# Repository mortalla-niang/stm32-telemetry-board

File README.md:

# STM32 Telemetry Board

> An end-to-end embedded systems project covering hardware design, firmware development, and desktop software for an STM32-based telemetry board.

---

# Overview

This project documents the complete development of an embedded telemetry board built around an STM32 microcontroller.

The objective is to design every part of the system from scratch while following industry-standard embedded development practices.

The project includes:

- Custom PCB design using KiCad
- STM32 firmware development in C
- Temperature acquisition through an I²C sensor
- UART communication with a desktop application
- Python desktop interface
- Complete engineering documentation
- Version control using Git

---

# System Architecture

```
                  USB-C
                    │
                    ▼
             +--------------+
             | 3.3V Regulator|
             +------+-------+
                    │
                    ▼
           +------------------+
           |  STM32C091KB MCU |
           +--------+---------+
                    │
         ┌──────────┴──────────┐
         │                     │
         ▼                     ▼
    TMP102 Sensor         UART Interface
      (I²C)                     │
                                ▼
                     Python Desktop Software
```

A more detailed architecture description is available in:

```
docs/System_Architecture.md
```

---
## Hardware Specifications

| Component | Selection |
|-----------|-----------|
| MCU | STM32C091KB |
| Temperature Sensor | TMP102 |
| Communication | UART |
| Sensor Interface | I²C |
| Power Supply | USB-C (5 V) |
| Operating Voltage | 3.3 V |
| PCB | 2 Layers |
| CAD Software | KiCad |

# Features

### Hardware

- STM32 microcontroller
- TMP102 digital temperature sensor
- USB powered
- 3.3V regulated supply
- UART communication
- I²C sensor interface
- Status LED

### Firmware

- Bare-metal C
- GPIO drivers
- I²C communication
- UART communication
- Periodic telemetry transmission

### Desktop Software

- Python application
- Real-time temperature display
- Telemetry monitoring
- Data logging *(planned)*

---

# Project Status

## Hardware

- [x] System specifications
- [x] Component selection
- [x] Schematic design
- [x] PCB layout
- [x] ERC verification
- [x] DRC verification
- [ ] PCB manufacturing
- [ ] Hardware validation

## Firmware

- [ ] STM32CubeMX configuration
- [ ] Clock configuration
- [ ] GPIO driver
- [ ] I²C driver
- [ ] UART driver
- [ ] Temperature acquisition
- [ ] Telemetry protocol

## Desktop Application

- [ ] User interface
- [ ] Live telemetry
- [ ] Data logging
- [ ] Graph visualization

---

# Repository Structure

```
docs/
│
├── Specifications.md
├── System_Architecture.md
├── Component_Selection.md
├── PCB_Design.md
└── Test_Plan.md

hardware/
│
├── kicad/
├── datasheets/
└── gerbers/

firmware/

software/

images/
```

---

# Technologies

- STM32
- KiCad
- C
- Python
- PySide6
- Git
- UART
- I²C
- USB

---

# Roadmap

## Version 1.0

- Complete PCB design
- Manufacture PCB
- Assemble components
- Develop firmware
- Read temperature sensor
- Display data on desktop application

## Future Improvements

- Additional sensors
- CAN communication
- RS-485 interface
- BLE connectivity
- Bootloader support
- FreeRTOS integration

---

# Documentation

Detailed design documents are available inside the `docs/` directory.

These documents include:

- System specifications
- Architecture
- Component selection
- PCB design choices
- Test plan

---

# License

This project is licensed under the MIT License.

---

# Author

**Mor Talla Niang**

Embedded Systems Engineer

France

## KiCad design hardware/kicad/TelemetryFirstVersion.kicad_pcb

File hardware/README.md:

# Hardware

KiCad project files, PCB layouts, schematics and manufacturing files.

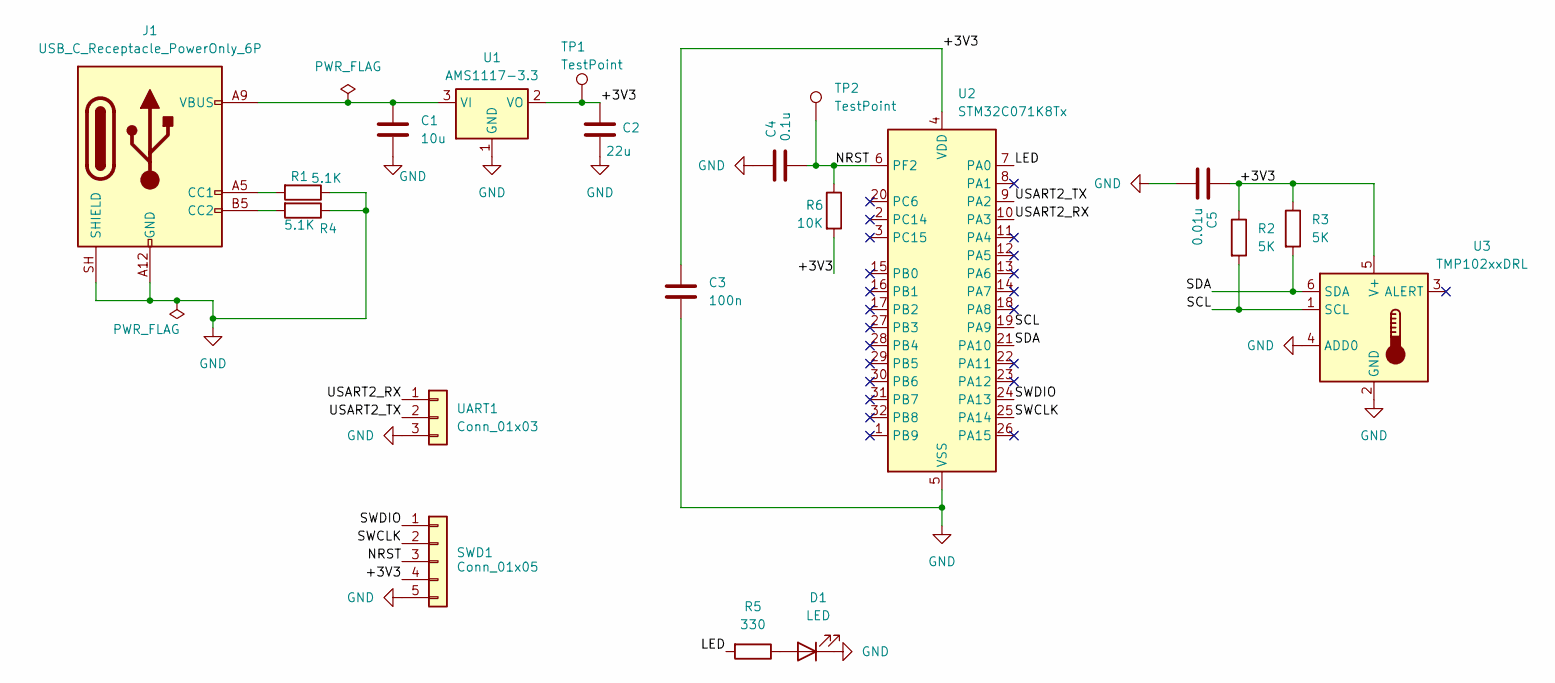
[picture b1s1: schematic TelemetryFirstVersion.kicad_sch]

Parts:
C1: 10u; C_0805_2012Metric
C2: 22u; C_0805_2012Metric
C3: 100n; C_0805_2012Metric
C4: 0.1u; C_0805_2012Metric
C5: 0.01u; C_0805_2012Metric
D1: LED; LED_0805_2012Metric
J1: USB_C_Receptacle_PowerOnly_6P; USB_C_Receptacle_GCT_USB4125-xx-x-0190_6P_TopMnt_Horizontal
R1, R4: 5.1K; R_0805_2012Metric
R2, R3: 5K; R_0805_2012Metric
R5: 330; R_0805_2012Metric
R6: 10K; R_0805_2012Metric
SWD1: Conn_01x05; PinHeader_1x05_P2.54mm_Vertical
TP1, TP2: TestPoint; TestPoint_Pad_D1.5mm
U1: AMS1117-3.3; SOT-223-3_TabPin2
U2: STM32C071K8Tx; LQFP-32_7x7mm_P0.8mm
U3: TMP102xxDRL; SOT-563
UART1: Conn_01x03; PinHeader_1x03_P2.54mm_Vertical

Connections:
/+3V3: C2.1, C3.1, C5.1, R2.1, R3.1, R6.2, SWD1.4, TP1.1 (1_1), U1.2 (VO), U2.4 (VDD), U3.5 (V+)
/LED: R5.2, U2.7 (PA0)
/NRST: C4.2, R6.1, SWD1.3, TP2.1 (1_1), U2.6 (PF2)
/SCL: R2.2, U2.19 (PA9), U3.1 (SCL)
/SDA: R3.2, U2.21 (PA10), U3.6 (SDA)
/SWCLK: SWD1.2, U2.25 (PA14)
/SWDIO: SWD1.1, U2.24 (PA13)
/USART2_RX: U2.10 (PA3), UART1.1
/USART2_TX: U2.9 (PA2), UART1.2
GND: C1.2, C2.2, C3.2, C4.1, C5.2, D1.1 (K), J1.A12 (GND), J1.B12 (GND), J1.SH (SHIELD), R1.1, R4.1, SWD1.5, U1.1 (GND), U2.5 (VSS), U3.2 (GND), U3.4 (ADD0), UART1.3
unnamed: D1.2 (A), R5.1
unnamed: J1.A5 (CC1), R1.2
unnamed: J1.B5 (CC2), R4.2
unnamed: C1.1, J1.A9 (VBUS), J1.B9 (VBUS), U1.3 (VI)

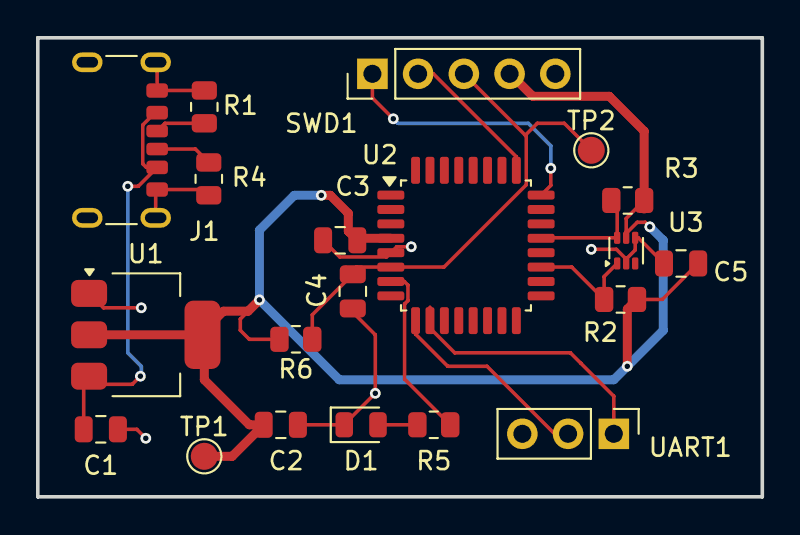
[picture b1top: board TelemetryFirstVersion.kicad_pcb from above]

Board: 2 copper layers, 40.2 x 25.5 mm, 20 parts (0 on the bottom side), 14 nets.
